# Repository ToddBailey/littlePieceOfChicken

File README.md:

# Little Piece Of Chicken
Bare Metal Development Board for NXP LPC1100XL (ARM Cortex M0) series parts.
Includes BOM and example code.

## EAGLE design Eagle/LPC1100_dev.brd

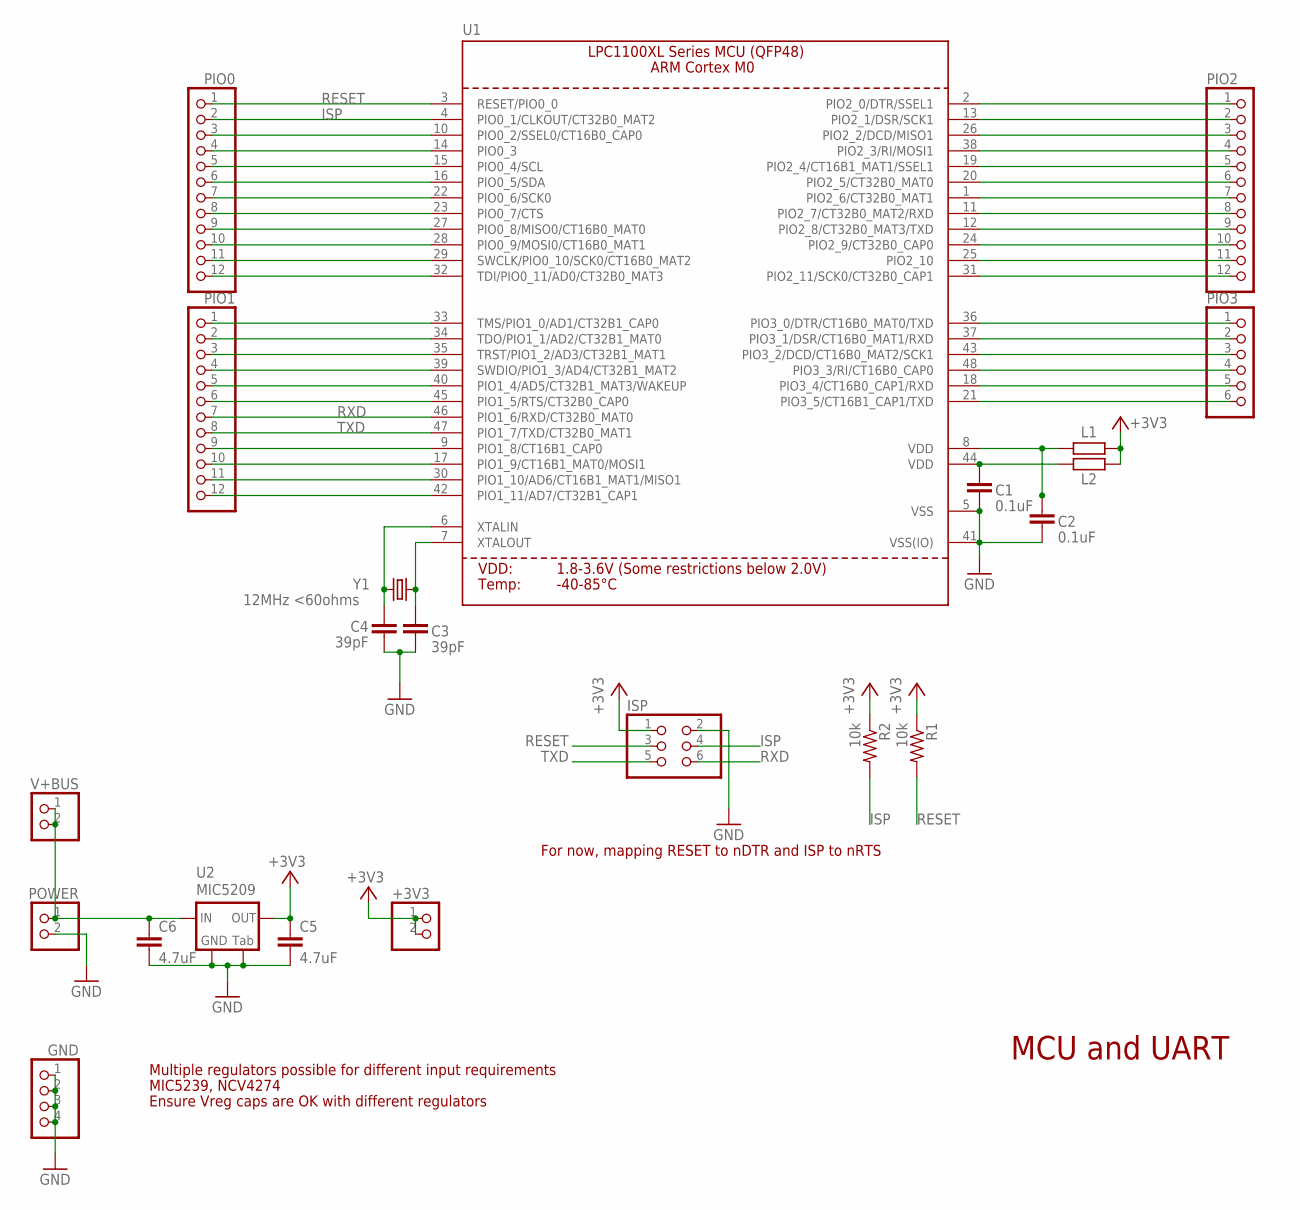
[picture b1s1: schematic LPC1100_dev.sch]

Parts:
+3V3: PINHD-1X2; 1X02
C1, C2: 0.1uF; C0603
C3, C4: 39pF; C0603
C5, C6: 4.7uF; C1210
GND: PINHD-1X4; 1X04
ISP: PINHD-2X3; 2X03
L1, L2: R-EU_R0603; R0603
PIO0, PIO1, PIO2: PINHD-1X12; 1X12
PIO3: PINHD-1X6; 1X06
POWER: PINHD-1X2; 1X02
R1, R2: 10k; R0603
U1: LPC1113/4/5_QFP48_XLSERIES; LQFP48
U2: MIC5209; SOT223
V+BUS: PINHD-1X2; 1X02
Y1: 12MHz <60ohms; HC49/S

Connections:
+3V3: +3V3.1, +3V3.2, C5.1, ISP.1, L1.1, L2.1, R1.1, R2.1, U2.3 (OUT)
CHARGE: PIO0.8, U1.23 (PIO0_7/CTS)
DDS_FSYNC: PIO0.3, U1.10 (PIO0_2/SSEL0/CT16B0_CAP0)
DDS_MCLK: PIO0.9, U1.27 (PIO0_8/MISO0/CT16B0_MAT0)
DDS_SCLK: PIO0.11, U1.29 (SWCLK/PIO0_10/SCK0/CT16B0_MAT2)
DDS_SDATA: PIO0.10, U1.28 (PIO0_9/MOSI0/CT16B0_MAT1)
FAULT: PIO1.10, U1.17 (PIO1_9/CT16B1_MAT0/MOSI1)
GND: C1.2, C2.2, C3.2, C4.2, C5.2, C6.2, GND.1, GND.2, GND.3, GND.4, ISP.2, POWER.2, U1.5 (VSS), U1.41 (VSS(IO)), U2.2 (GND), U2.4 (TAB)
ISP: ISP.4, PIO0.2, R2.2, U1.4 (PIO0_1/CLKOUT/CT32B0_MAT2)
MEGGER_GAIN: PIO2.12, U1.31 (PIO2_11/SCK0/CT32B0_CAP1)
MEGGER_I: PIO1.11, U1.30 (PIO1_10/AD6/CT16B1_MAT1/MISO1)
MEGGER_V: PIO0.12, U1.32 (TDI/PIO0_11/AD0/CT32B0_MAT3)
unnamed: PIO0.5, U1.15 (PIO0_4/SCL)
unnamed: C6.1, POWER.1, U2.1 (IN), V+BUS.1, V+BUS.2
unnamed: PIO0.6, U1.16 (PIO0_5/SDA)
unnamed: PIO1.9, U1.9 (PIO1_8/CT16B1_CAP0)
unnamed: PIO2.1, U1.2 (PIO2_0/DTR/SSEL1)
unnamed: PIO2.4, U1.38 (PIO2_3/RI/MOSI1)
unnamed: PIO2.5, U1.19 (PIO2_4/CT16B1_MAT1/SSEL1)
unnamed: PIO2.10, U1.24 (PIO2_9/CT32B0_CAP0)
unnamed: PIO2.11, U1.25 (PIO2_10)
unnamed: PIO3.1, U1.36 (PIO3_0/DTR/CT16B0_MAT0/TXD)
unnamed: PIO3.3, U1.43 (PIO3_2/DCD/CT16B0_MAT2/SCK1)
unnamed: PIO3.4, U1.48 (PIO3_3/RI/CT16B0_CAP0)
unnamed: PIO3.5, U1.18 (PIO3_4/CT16B0_CAP1/RXD)
unnamed: PIO3.6, U1.21 (PIO3_5/CT16B1_CAP1/TXD)
unnamed: C3.1, U1.7 (XTALOUT), Y1.2
unnamed: C4.1, U1.6 (XTALIN), Y1.1
unnamed: C1.1, L2.2, U1.44 (VDD)
unnamed: C2.1, L1.2, U1.8 (VDD)
unnamed: PIO3.2, U1.37 (PIO3_1/DSR/CT16B0_MAT1/RXD)
unnamed: PIO2.7, U1.1 (PIO2_6/CT32B0_MAT1)
unnamed: PIO1.6, U1.45 (PIO1_5/RTS/CT32B0_CAP0)
PEAK_RESET: PIO1.2, U1.34 (TDO/PIO1_1/AD2/CT32B1_MAT0)
PHONE_MUX_DATA: PIO2.8, U1.11 (PIO2_7/CT32B0_MAT2/RXD)
PHONE_MUX_LATCH: PIO2.9, U1.12 (PIO2_8/CT32B0_MAT3/TXD)
PHONE_MUX_OE: PIO0.4, U1.14 (PIO0_3)
PHONE_MUX_SCK: PIO2.2, U1.13 (PIO2_1/DSR/SCK1)
RESET: ISP.3, PIO0.1, R1.2, U1.3 (RESET/PIO0_0)
RXD: ISP.6, PIO1.7, U1.46 (PIO1_6/RXD/CT32B0_MAT0)
TXD: ISP.5, PIO1.8, U1.47 (PIO1_7/TXD/CT32B0_MAT1)
VR_POL: PIO1.12, U1.42 (PIO1_11/AD7/CT32B1_CAP1)
VX_POL: PIO1.1, U1.33 (TMS/PIO1_0/AD1/CT32B1_CAP0)
Z_DC_SELECT: PIO2.3, U1.26 (PIO2_2/DCD/MISO1)
Z_I: PIO1.4, U1.39 (SWDIO/PIO1_3/AD4/CT32B1_MAT2)
Z_I_GAIN: PIO1.5, U1.40 (PIO1_4/AD5/CT32B1_MAT3/WAKEUP)
Z_MEG_MUX: PIO0.7, U1.22 (PIO0_6/SCK0)
Z_SHDN: PIO2.6, U1.20 (PIO2_5/CT32B0_MAT0)
Z_V: PIO1.3, U1.35 (TRST/PIO1_2/AD3/CT32B1_MAT1)

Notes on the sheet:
MCU and UART
For now, mapping RESET to nDTR and ISP to nRTS
Multiple regulators possible for different input requirements
MIC5239, NCV4274
Ensure Vreg caps are OK with different regulators

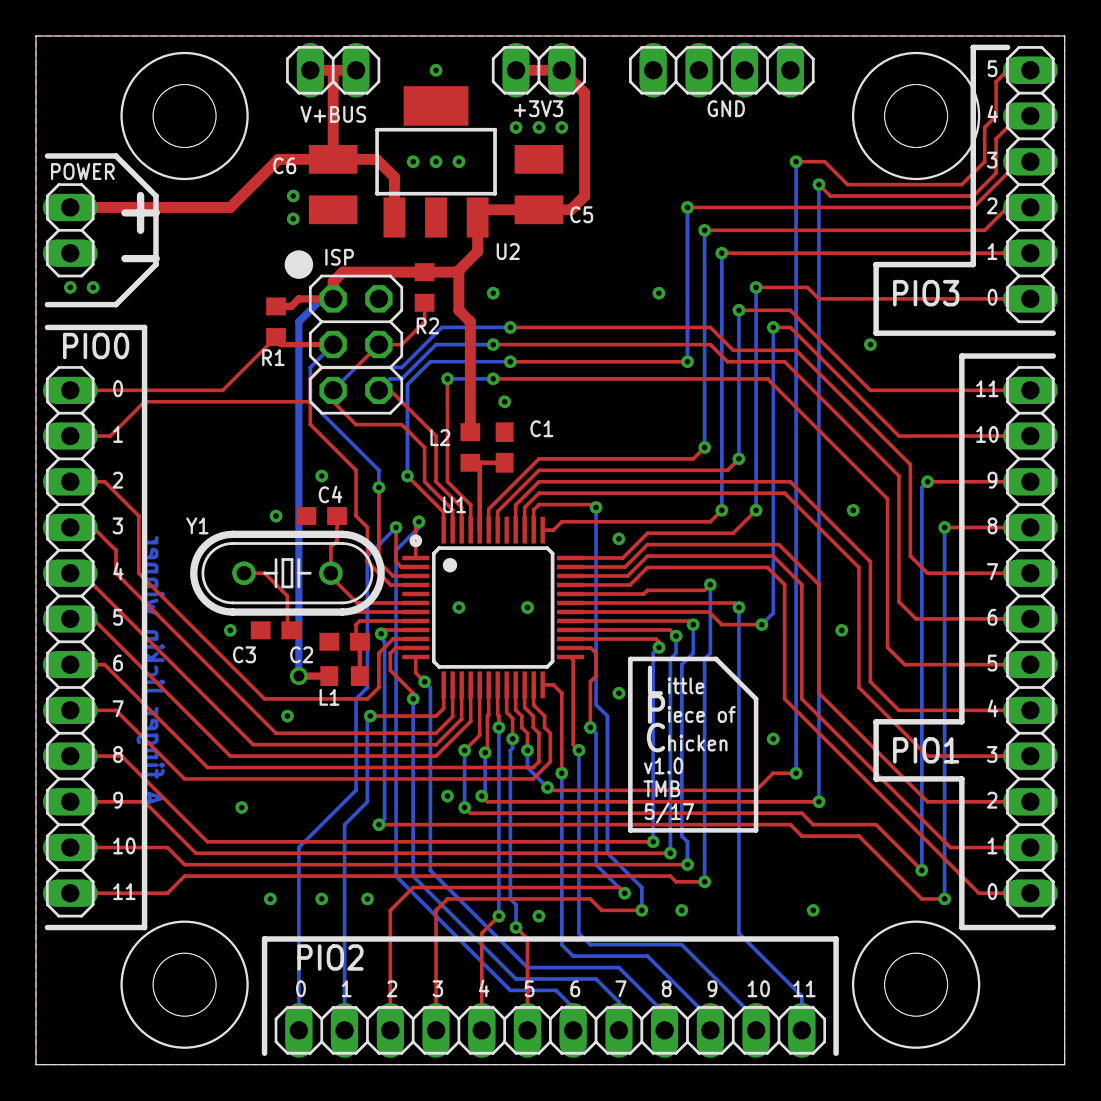
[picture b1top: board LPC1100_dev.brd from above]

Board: 2 copper layers, 57.1 x 57.1 mm, 26 parts (0 on the bottom side), 49 nets.

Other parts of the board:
U$1, U$2, U$3, U$4: 6X32_HOLE

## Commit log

2017-05-10 Initial commit, hardware only
2017-05-10 Added images, updated README
2017-05-10 Added BOM w/ Digikey numbers

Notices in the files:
parts and their libraries:
microbuilder: This work is placed in the public domain, and may be freely used for commercial and non-commercial work with the following conditions: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
